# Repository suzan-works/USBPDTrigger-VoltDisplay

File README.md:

# 電圧表示付き USB PD トリガー
 WCH CH32X035 マイコンを使用して、Vbus電圧をSSD1306 OLEDモジュールに表示する、USB PDトリガーデバイスです。  

# 紹介動画

# 操作手順
1. USB-CコネクタにUSB PD電源を接続します。
1. 電圧切替スイッチで出力電圧を変更します。(5→9→12→15→20Vのループ)
1. OLEDディスプレイで希望の電圧が出ていることを確認します。
1. 出力入切スイッチを押すと基板右端のヘッダピンから出力されます。  

# 注意
- 出力電圧はUSB電源(USB PD Source)の仕様に依存します。設定電圧とVbus電圧が乖離する場合があります。
- 表示されるVbus電圧は目安で、測定器としての精度を保証するものではありません。
- 出力電流は1A程度を想定して設計しています。
- このデバイスの使用における損害は一切保証いたしません。自己責任でご使用ください。

# 販売
[boothにて販売中](https://suzan-works.booth.pm/items/5385432)

# マイコン開発
Arduino IDEでのファームウェア変更が可能です。  
WCH LinkEエミュレーターでPCに接続して、「ボードマネージャ」＞「CH32V EVT Boards Support」＞「CH32X035」を選択します。  
参考情報  
https://github.com/openwch/arduino_core_ch32  
https://youtu.be/PSXAfMaWH_A?si=gFLTGL1ydqfZDPP8  

# 設計資料 v1.0
## 回路図
- 回路図 [PDF](回路図.pdf) [KiCanvas](https://kicanvas.org/?github=https%3A%2F%2Fgithub.com%2Fsuzan-works%2FUSBPDTrigger-VoltDisplay%2Fblob%2Fmain%2FKiCad%2FCH32X035_USBPD-Trigger_4.kicad_sch)  
- BOM

|Reference|Value|ECサイト|コメント|
|:----|:----|:----|:----|
|U1|マイコン<br>CH32X035G8U6| | |
|U2|三端子レギュレータ<br>NJM78L33SU3|https://akizukidenshi.com/catalog/g/gI-11319/| |
|J1|USB Type-Cコネクタ 電源供給用|https://akizukidenshi.com/catalog/g/gC-16438/|コネクタの固定用ピンをカットして実装しています|
|J2|OLEDディスプレイ<br>SSD1306 SPI 128x32 0.91インチ| | |
|J3, J4, J6, J7|ピンヘッダ 2.54mmピッチ|https://akizukidenshi.com/catalog/g/gC-00167/| |
|J5|WCH-LinkE| | |
|C1, C2|1u/50V/2012|https://akizukidenshi.com/catalog/g/gP-15331/| |
|C3|1u/25V/1608|https://akizukidenshi.com/catalog/g/gP-14526/| |
|R1, R4|220/1608/±5%| | |
|R2|10k/1608/±1%|https://www.marutsu.co.jp/pc/i/857775/| |
|R3|1k/1608/±1%|https://www.marutsu.co.jp/pc/i/857774/| |
|R5|10k/1608/±5%| | |
|R6|22k/1608/±5%| | |
|R7, R8|5.1k/1608/±5%| | |
|D1|緑チップLED<br>SML-E12P8WT86|https://akizukidenshi.com/catalog/g/gI-11878/| |
|D2|赤チップLED<br>SML-E12V8WT86|https://akizukidenshi.com/catalog/g/gI-11879/| |
|F1|ポリスイッチ<br>microSMD010|https://akizukidenshi.com/catalog/g/gP-01316/| |
|Q1, Q2|Pch MOSFET<br>AO3401A|https://akizukidenshi.com/catalog/g/gI-14654/| |
|Q3|抵抗入りトランジスタ<br>DTC143ZU3HZGT106|https://akizukidenshi.com/catalog/g/gI-16746/|基板フットプリントが間違っており無理やり実装しています|
|SW1, SW2|タクトスイッチ<br>SKRPABE010|https://akizukidenshi.com/catalog/g/gP-06184/| |

## プリント基板
- 基板CAD [KiCanvas](https://kicanvas.org/?github=https%3A%2F%2Fgithub.com%2Fsuzan-works%2FUSBPDTrigger-VoltDisplay%2Fblob%2Fmain%2FKiCad%2FCH32X035_USBPD-Trigger_5.kicad_pcb)
- 外観写真  

## ファームウェア
- ファームウェア [inoファイル](USBPDTrigger-VoltDisplay.ino)

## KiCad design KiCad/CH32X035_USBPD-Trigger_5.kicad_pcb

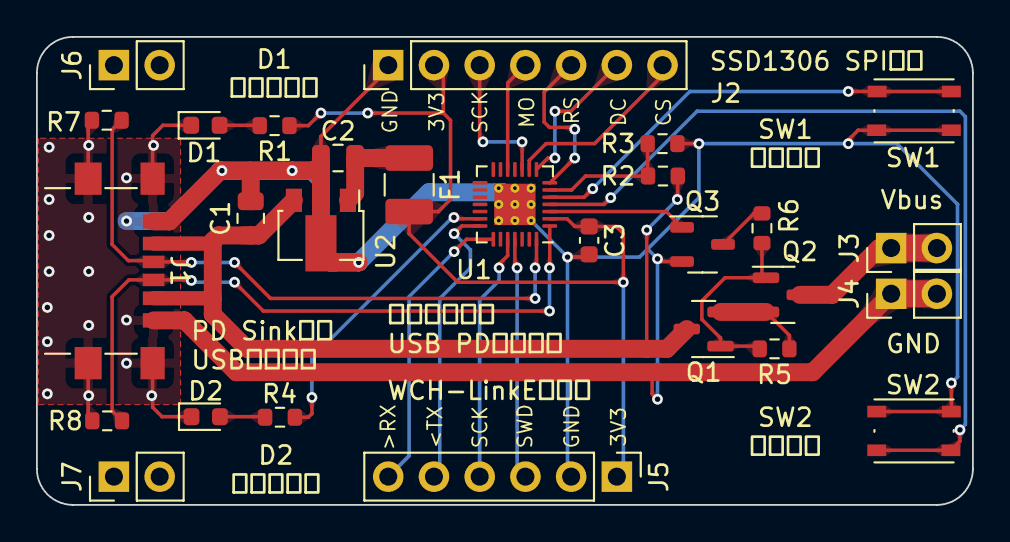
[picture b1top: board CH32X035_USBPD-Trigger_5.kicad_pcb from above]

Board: 2 copper layers, 52.0 x 26.0 mm, 28 parts (0 on the bottom side), 26 nets.

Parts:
C1, C2: C_Small; C_0805_2012Metric
C3: C_Small; C_0603_1608Metric
D1, D2: LED; LED_0603_1608Metric
F1: Polyfuse_Small; Fuse_1210_3225Metric_Pad1.42x2.65mm_HandSolder
J1: USB_C_Receptacle_PowerOnly_6P; USB_C_Receptacle_GCT_USB4135-GF-A_6P_TopMnt_Horizontal
J2: Conn_01x07; PinHeader_1x07_P2.54mm_Vertical
J3, J4, J6, J7: Conn_01x02; PinHeader_1x02_P2.54mm_Vertical
J5: Conn_01x06; PinHeader_1x06_P2.54mm_Vertical
Q1, Q2: Q_PMOS_GSD; SOT-23
Q3: DTC143Z; SOT-23-3
R1, R2, R3, R4, R5, R6: R_Small; R_0603_1608Metric
R7, R8: 5.1k; R_0603_1608Metric
SW1, SW2: SW_Push; SW_Push_1P1T_NO_Vertical_Wuerth_434133025816
U1: CH32X035G8U6; QFN-28-1EP_4x4mm_P0.4mm_EP2.3x2.3mm_ThermalVias
U2: L78L33_SOT89; SOT-89-3

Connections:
+3.3V: C3.1, F1.2, J2.2, J5.1, R1.1, U1.2 (VDD)
/BTN_A: SW1.2, U1.5 (PA0)
/BTN_B: SW2.2, U1.4 (PC3)
/CC1: J1.A5 (CC1), R7.1, U1.28 (PC14/CC1)
/CC2: J1.B5 (CC2), R8.1, U1.1 (PC15/CC2)
/CS: J2.7, U1.9 (PA4/CS)
/LED: R4.1, U1.20 (PB9)
/MOSI: J2.4, U1.12 (PA7/MOSI)
/OLED_DC: J2.6, U1.8 (PA3)
/OLED_RST: J2.5, U1.7 (PA2)
/OUTPUT: Q3.1 (B), U1.3 (PC0)
/RXIN: J5.6, U1.22 (PB11/RX)
/SCK: J2.3, U1.10 (PA5/SCK)
/SWCLK: J5.4, U1.24 (PC19/DCK)
/SWDIO: J5.3, U1.25 (PC18/DIO)
/TXOUT: J5.5, U1.21 (PB10/TX)
/VBUS_DIV: R2.2, R3.1, U1.6 (PA1)
GND: C1.2, C2.2, C3.2, D1.1 (K), D2.1 (K), J1.A12 (GND), J1.B12 (GND), J1.S1 (SHIELD), J2.1, J4.1, J4.2, J5.2, Q3.2 (E), R3.2, R7.2, R8.2, SW1.1, SW2.1, U1.29 (GND), U2.2 (GND)
unnamed: D1.2 (A), R1.2
unnamed: D2.2 (A), R4.2
unnamed: J3.1, J3.2, Q2.3 (D)
unnamed: Q1.1 (G), Q2.1 (G), R5.2, R6.1
unnamed: Q1.2 (S), Q2.2 (S), R5.1
unnamed: Q3.3 (C), R6.2
unnamed: C2.1, F1.1, U2.1 (OUT)
VBUS: C1.1, J1.A9 (VBUS), J1.B9 (VBUS), Q1.3 (D), R2.1, U2.3 (IN)

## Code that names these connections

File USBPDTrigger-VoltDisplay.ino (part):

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// PD出力設定番号、0=5V,1=9V,2=12V,3=15V,4=20V
int pdNum = 0;

#define OLED_CS PA4
#define OLED_DC PA3
#define OLED_RESET PA2

#define btnAPin D0
#define btnBPin D20
#define vbusDividedPin PA1
#define outputPin PC0
#define ledPin D15

bool isLight = 0;
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void setup()
{
	pinMode(OLED_CS, OUTPUT);
	pinMode(OLED_DC, OUTPUT);
	pinMode(OLED_RESET, OUTPUT);

	pinMode(btnAPin, INPUT_PULLUP);
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
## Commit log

2023-12-30 ファイルアップロード
2023-12-30 README追記
2024-01-08 BOM追記
2024-01-08 KiCadファイル追加
2024-01-08 KiCanvas表示追加
2024-03-10 動作改善のためのファームウェア更新
    ・ボタン入力のチャタリング防止
    ・表示電圧を現物合わせで調整
    上記を実装しました。
2024-05-09 ファームウェア更新とREADME追記
    ・ファームウェア：電圧測定に平均化処理を追加
    ・README：紹介動画と販売場所のリンクを追記
